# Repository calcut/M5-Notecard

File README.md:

A KiCAD project for a PCB to interface a Blues Wireless Notecard to M5 Stack Core2
Should also work with CoreS3

Intended to fit into a [M5 Base26](https://shop.m5stack.com/products/base26-proto-industrial-board-module-v1-1)

Features Include
- Enables "Outboard DFU", from Notecard to ESP32
- RS485 interface for industrial modbus connections
- 12/24V to 5V buck regulator

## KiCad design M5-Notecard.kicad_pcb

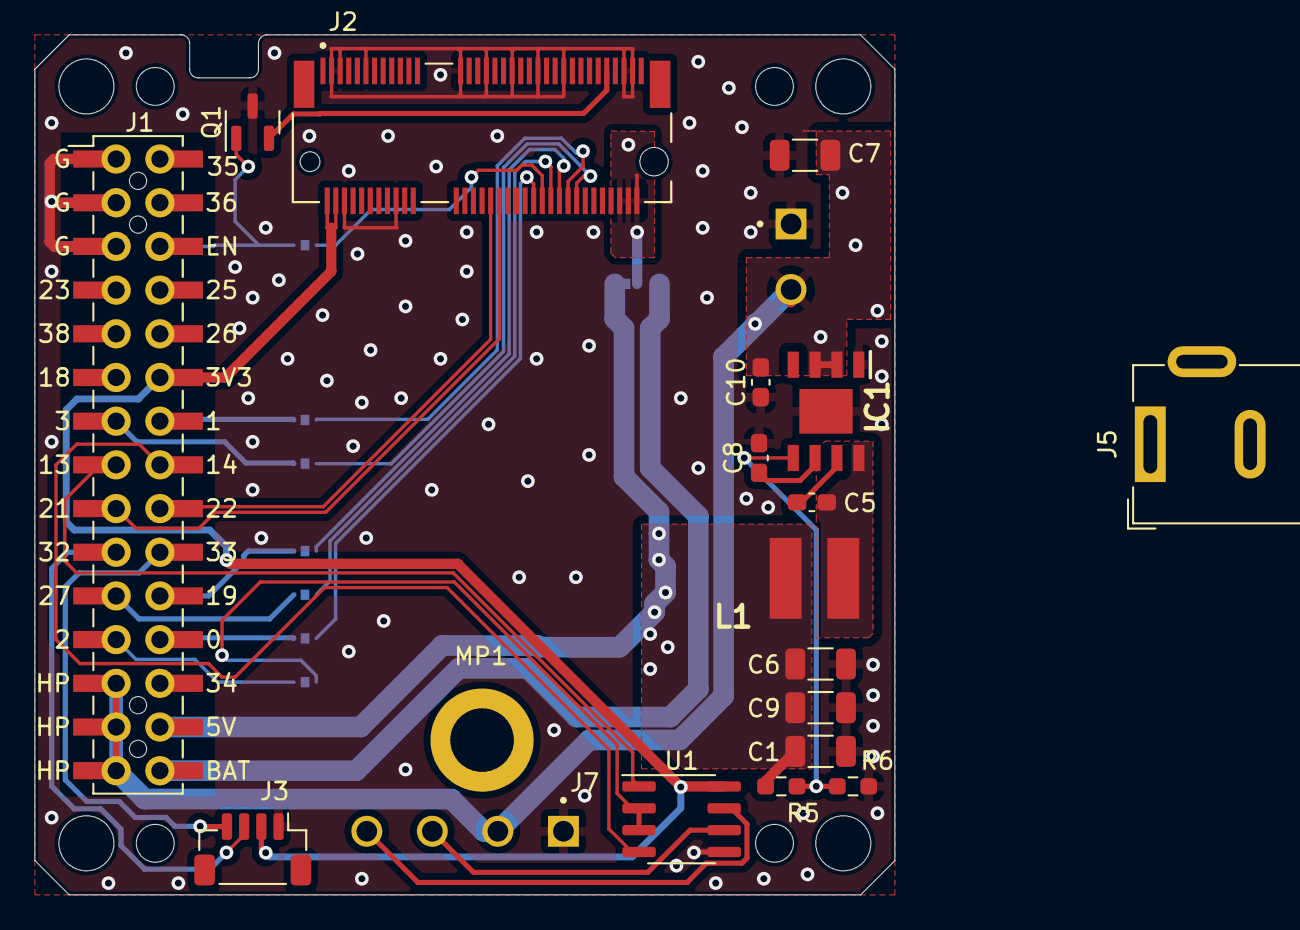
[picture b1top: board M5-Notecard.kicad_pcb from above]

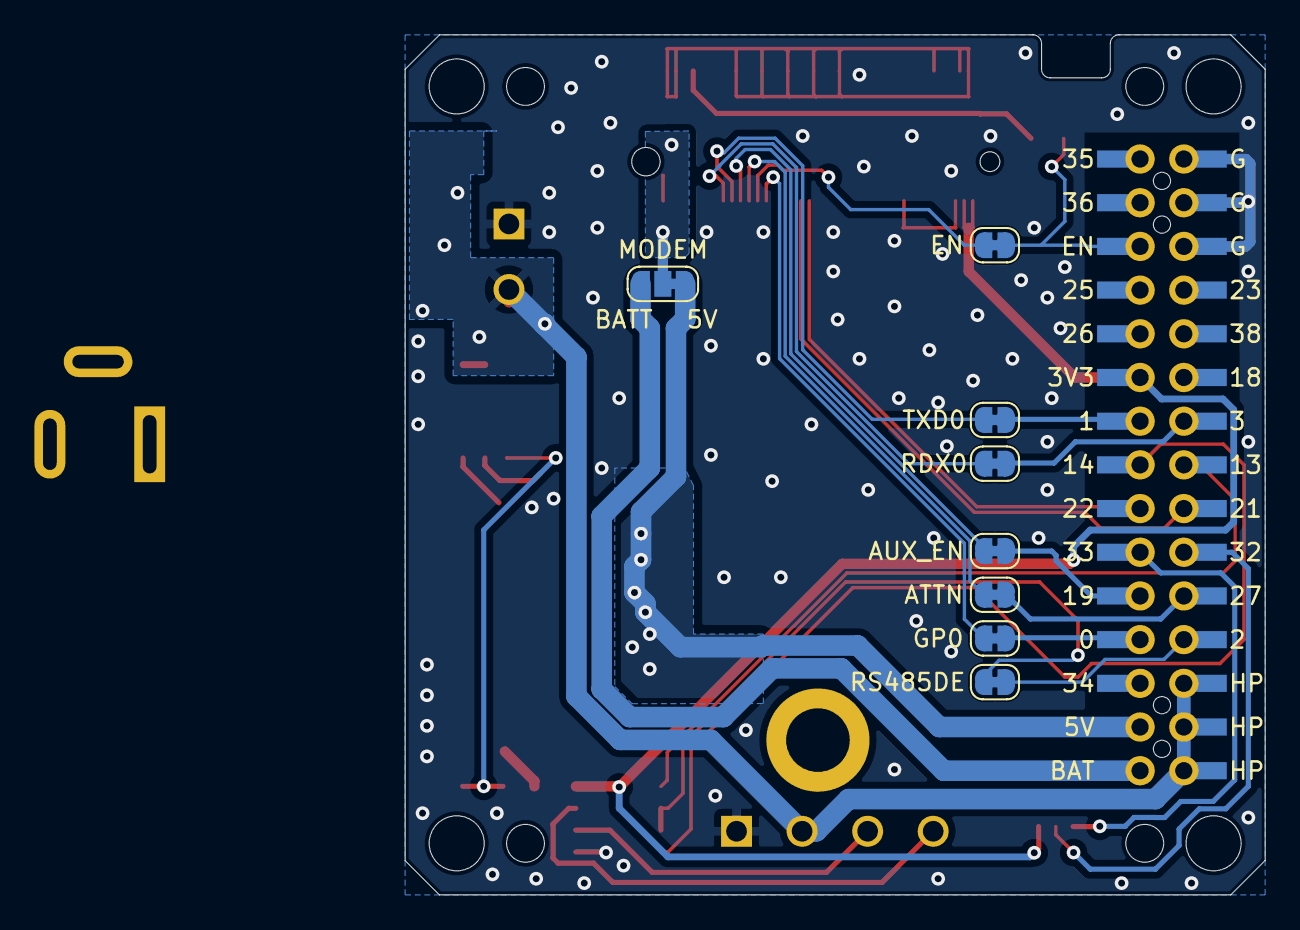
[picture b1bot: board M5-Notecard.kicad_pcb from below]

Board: 2 copper layers, 50.0 x 50.0 mm, 36 parts (8 on the bottom side), 33 nets.

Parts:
C1, C6, C7, C9: 22uF; C_1206_3216Metric
C5: 0.1uF; C_0603_1608Metric_Pad1.08x0.95mm_HandSolder
C8: 1uF; C_0603_1608Metric_Pad1.08x0.95mm_HandSolder
C10: 220nF; C_0603_1608Metric_Pad1.08x0.95mm_HandSolder
H1, H2, H3, H4: MountingHole; BF@MountingHole_3.2mm_M3
H5, H6, H7, H8: MountingHole; BF@MountingHole_2.2mm_M2
IC1: LMR33630CDDAR; SOIC127P600X170-9N
J1: M-BUS; BF@M5Stack_MBUS_CORE2
J2: Bus_M.2_Socket_E; AMPHENOL_MDT420E01001_Notecard
J3: 110990030; JST_SH_BM04B-SRSS-TB_1x04-1MP_P1.00mm_Vertical
J5: Barrel_Jack; BarrelJack_Wuerth_6941xx301002
J6: 284513-2; TE_284513-2
J7: 284513-4; TE_284513-4
JP1, JP2, JP3, JP4, JP6, JP7, JP8: SolderJumper_2_Bridged; SolderJumper-2_P1.3mm_Bridged_RoundedPad1.0x1.5mm
JP5: SolderJumper_3_Bridged12; SolderJumper-3_P1.3mm_Bridged12_RoundedPad1.0x1.5mm_NumberL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
L1: XAL5030-601MEB; Coilcraft_50xx-40xx_hybrid
MP1: 9774025151R; WE_9774025151R
Q1: BC856; SOT-23
R5: 100K; R_0603_1608Metric_Pad0.98x0.95mm_HandSolder
R6: 24.9K; R_0603_1608Metric_Pad0.98x0.95mm_HandSolder
U1: SP3481EN; SOIC-8_3.9x4.9mm_P1.27mm

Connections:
+3V3: J1.11, J2.2 (VIO_P), J2.4 (VIO_P), J3.2, U1.8 (VCC)
+5V: C1.1, C6.1, C9.1, J1.27, JP5.1 (A), L1.2, R5.1
+12V: C7.1, C10.2, IC1.2 (VIN), IC1.3 (EN), J1.26, J1.28, J1.30, J6.2, J7.2
+BATT: J1.29, JP5.3 (B)
/ATTN: J1.22, JP2.1 (A)
/AUX_EN: J1.21, JP4.1 (A)
/BOOT: C5.1, IC1.7 (BOOT)
/EN: J1.5, JP7.1 (A), Q1.1 (B)
/FB: IC1.5 (FB), R5.2, R6.1
/GPIO0: J1.23, JP6.1 (A)
/RS485_A: J7.3, U1.6 (A)
/RS485_B: J7.4, U1.7 (B)
/RS485_DE: J1.24, JP8.1 (A)
/RXD0: J1.14, JP1.1 (A)
/RXD2: J1.16, U1.1 (RO)
/SW: C5.2, IC1.8 (SW), L1.1
/TXD0: J1.13, JP3.1 (A)
/TXD2: J1.15, U1.4 (DI)
/VCC: C8.2, IC1.6 (VCC)
/VMODEM: J2.70 (VMODEM_P), J2.72 (VMODEM_P), J2.74 (VMODEM_P), JP5.2 (C)
/extSCL: J1.19, J3.4
/extSDA: J1.20, J3.3
/intSCL: J1.17, J2.40 (SCL_P)
/intSDA: J1.18, J2.42 (SDA_P)
GND: C1.2, C6.2, C7.2, C8.1, C9.2, C10.1, IC1.1 (PGND), IC1.9 (AGND), J1.2, J1.4, J1.6, J2.3 (GND), J2.5 (GND), J2.6 (GND), J2.11 (GND), J2.18 (GND), J2.33 (GND), J2.39 (GND), J2.45 (GND), J2.51 (GND), J2.57 (GND), J2.71 (GND), J2.73 (GND), J3.1, J6.1, J7.1, Q1.3 (C), R6.2, U1.5 (GND)
unnamed: J2.54 (ATTN_P), JP2.2 (B)
unnamed: J2.50 (AUX3), JP6.2 (B)
unnamed: J2.52 (AUX4), JP7.2 (B)
unnamed: J2.56 (AUX_EN_P), JP4.2 (B)
unnamed: J2.58 (AUX_RX_P), JP3.2 (B)
unnamed: J2.60 (AUX_TX_P), JP1.2 (B)
unnamed: J2.67 (NRST), Q1.2 (E)
unnamed: JP8.2 (B), U1.2 (~RE), U1.3 (DE)

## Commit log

2023-07-25 added 3d png
2023-07-25 added a readme

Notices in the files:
M5-Notecard.kicad_pcb:
Copyright 2022 BotanicFields, Inc.
